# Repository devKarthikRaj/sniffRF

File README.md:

# sniffRF

## Project Snapshot
| Spec | Details |
|---|---|
| MCU | STM32L053R8 (M0+) |
| Firmware | Written in C++ via STM32CubeIDE |
| RF Detector | AD8318 Logarithmic (RF Power) Detector |
| Frequency Range | 902-928 MHz |
| Measurement Method | RF power -> Analog Voltage -> STM32 ADC |
| Power System | Li-ion battery with BQ24074 power path manager (charger included) |
| Display | OLED (SSD1306) |
| PCB | 4-layer mixed signal PCB designed in KiCad |
| Manufacturing | PCB fabrication and assembly done by JLCPCB |
| Cost | S$250 |
| Status | Hardware bring-up completed, core functionality validated (excluding OLED) |

 <br>
 <br>
 <br>
 <br>

## About
SniffRF is a simple RSSI detector aka a signal strength detector for the 902MHz to 928MHz band using an AD8318 logarithmic detector chip and built around an STM32L053R8 MCU. SniffRF displays the RSSI level on a mini OLED. SniffRF will also pulse a buzzer with varying frequency based on the RSSI level. <br>

## Sub-Systems
* RF: Input from SMA fed into AD8318 log detector. <br>
* MCU: STM32L053R8 M0+ interface circuitry, program/debug MCU via SWD.
* UI: OLED for visual feedback and buzzer for audio feedback.
* Power: 1x 18650 cell with BQ24074 power path manager, charge via USB-C, MAX1704 fuel gauge, simple buck converter for 3.3V

## Application
* SniffRF could be used to track RF transmitters using their radio signature. <br>
* SniffRF could also be used to gauge the noise floor at a particular location to select or deploy a receiver at said location. <br>   

*Note: As of now, SniffRF only tunes into the 902-928MHz band.*

## Bring-Up and Validation
* **STM32 MCU able to boot up and connect via J-Link debugger to STM32CubeIDE.** STM32 UART connection working as expected. <br>
* **AD8318 RSSI detection circuit is fully functional from about -60dBm to 0dBm. A known RF source (Sine wave transmitted at 915MHz from an Adalm Pluto SDR) was moved toward and away from the SniffRF PCB - this caused the RSSI readings to increase and decrease as expected.** <br>
* Li-Ion battery power path manager is able to charge the 18650 battery when a USB-C charge cable is plugged in. MAX1704 fuel gauge is able to read Li-Ion battery voltage + capacity and send this data over to the STM32 for display over UART. <br>
* Buzzer interfaced to STM32 is functional. <br>
* Unable to verify OLED functionality due to lack of assembled SniffRF boards, TBC... <br>

## Thoughts...
This is my first STM32 PCB! I made this PCB to learn STM32 design as well as try my hand at mixed signal PCB design. Feels good to finally strike this off my bucket list. Spent a few weekends working on this project over 3 months. More advanced RF PCBs to come!

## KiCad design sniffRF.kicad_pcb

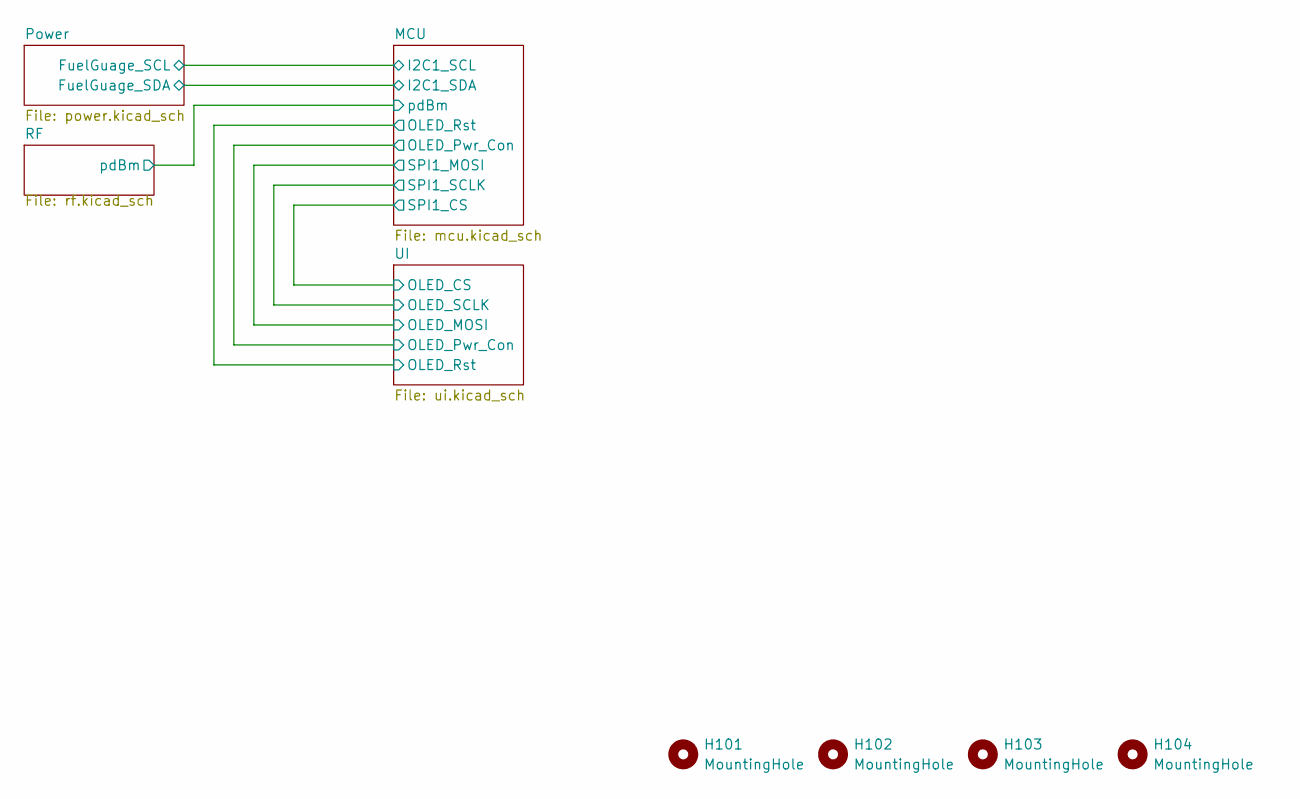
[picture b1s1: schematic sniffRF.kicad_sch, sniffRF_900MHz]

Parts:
H101, H102, H103, H104: MountingHole; MountingHole_PC104_Reinforced

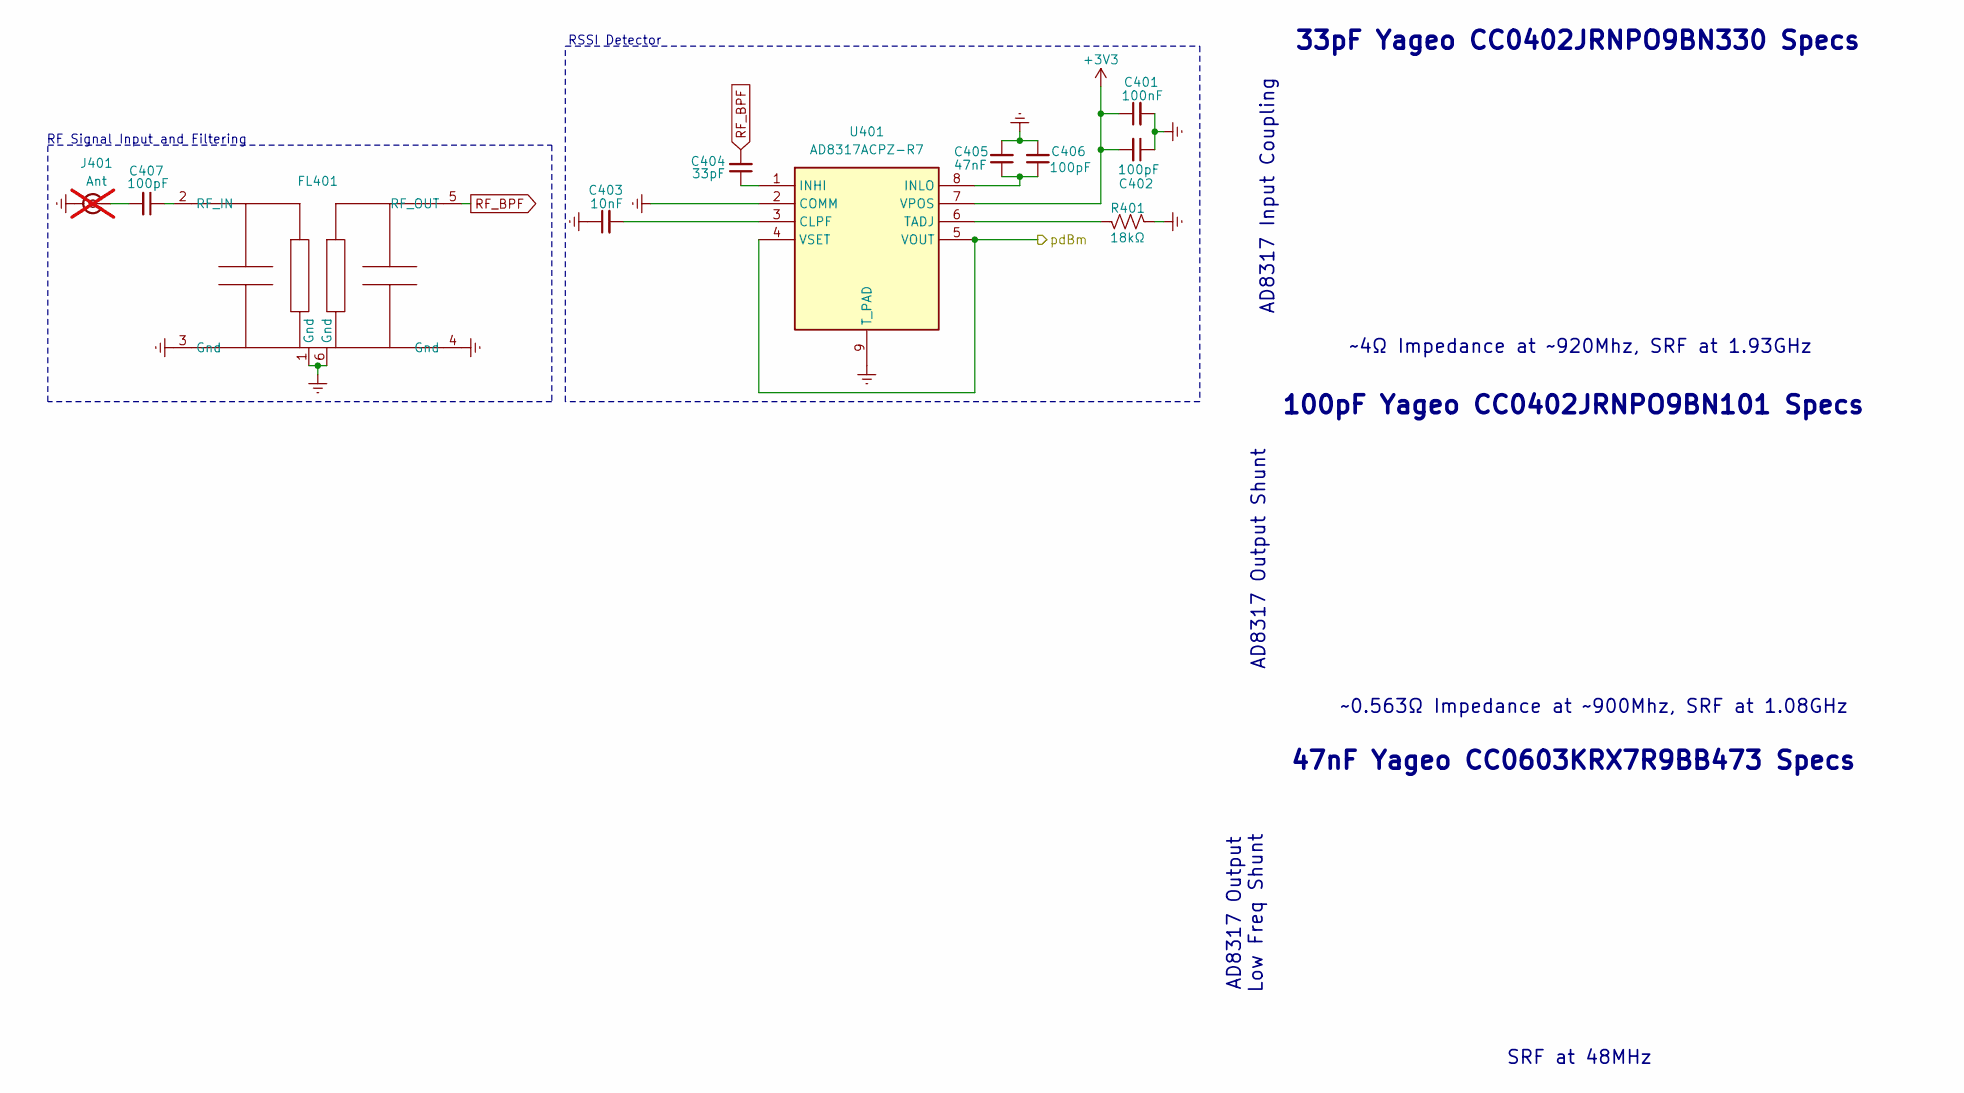
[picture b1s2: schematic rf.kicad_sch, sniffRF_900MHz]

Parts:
C401: 100nF; C_0402_1005Metric_Pad0.74x0.62mm_HandSolder; MPN CL05B104KO5NNNC; LCSC PN C1525
C402, C406, C407: 100pF; C_0402_1005Metric_Pad0.74x0.62mm_HandSolder; MPN CC0402JRNPO9BN101; LCSC PN C106200
C403: 10nF; C_0805_2012Metric_Pad1.18x1.45mm_HandSolder; MPN CC0805KRX7R9BB103; LCSC PN C83170
C404: 33pF; C_0402_1005Metric_Pad0.74x0.62mm_HandSolder; MPN CC0402JRNPO9BN330; LCSC PN C107005
C405: 47nF; C_0603_1608Metric_Pad1.08x0.95mm_HandSolder; MPN CC0603KRX7R9BB473; LCSC PN C107093
FL401: BPF_Qualcomm_B39921B3728U410; MPN B39921B3728U410; LCSC PN C2650953
J401: Ant; SMA_Cinch_142-0701-851; MPN 142-0701-801; not fitted
R401: 18kΩ; R_0603_1608Metric_Pad0.98x0.95mm_HandSolder; MPN 0603WAF1802T5E; LCSC PN C25810
U401: AD8317ACPZ-R7; RssiDet_AnalogDevices_SON50P200X300X80-9N-D; Manufacturer_Part_Number AD8317ACPZ-R7; Mouser Part Number 584-AD8317ACPZ-R7

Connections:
+3V3: C401.1, C402.2, U401.7 (VPOS); also elsewhere on the board
/MCU/pdBm: U401.4 (VSET), U401.5 (VOUT); also elsewhere on the board
GNDREF: C401.2, C402.1, C403.1, C405.2, C406.2, FL401.1 (Gnd), FL401.3 (Gnd), FL401.4 (Gnd), FL401.6 (Gnd), J401.2 (Ext), R401.2, U401.2 (COMM), U401.9 (T_PAD); also elsewhere on the board
unnamed: C407.1, FL401.2 (RF_IN)
unnamed: C407.2, J401.1 (In)
unnamed: C403.2, U401.3 (CLPF)
unnamed: C404.1, U401.1 (INHI)
unnamed: C405.1, C406.1, U401.8 (INLO)
unnamed: R401.1, U401.6 (TADJ)
RF_BPF: C404.2, FL401.5 (RF_OUT)

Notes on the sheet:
AD8317 Output Shunt
33pF Yageo CC0402JRNPO9BN330 Specs
47nF Yageo CC0603KRX7R9BB473 Specs
100pF Yageo CC0402JRNPO9BN101 Specs
~4Ω Impedance at ~920Mhz, SRF at 1.93GHz
AD8317 Output Low Freq Shunt
RF Signal Input and Filtering
~0.563Ω Impedance at ~900Mhz, SRF at 1.08GHz
SRF at 48MHz
AD8317 Input Coupling
RSSI Detector

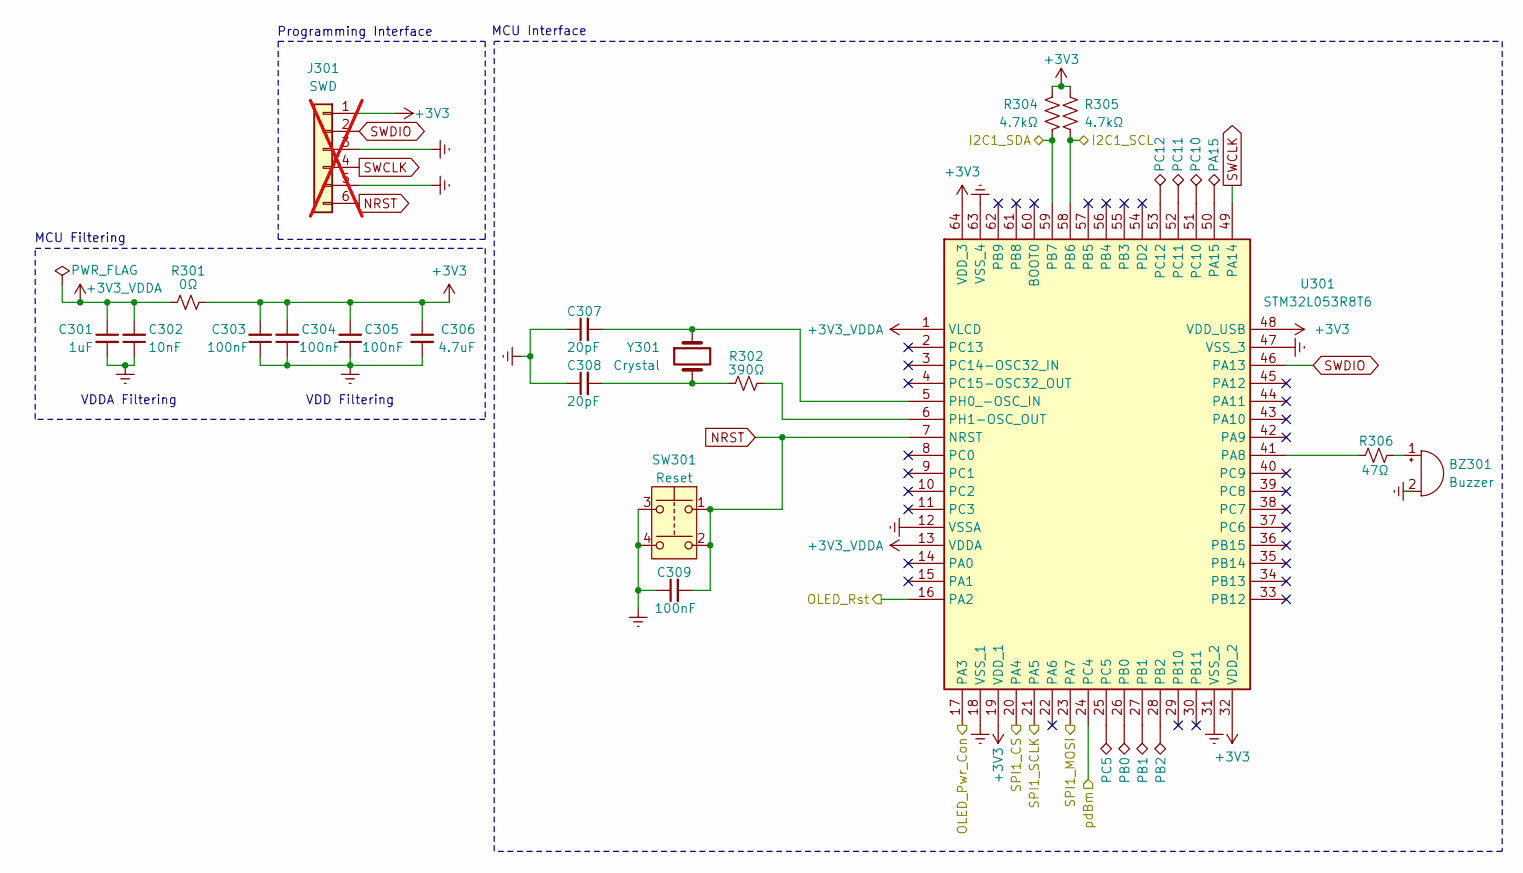
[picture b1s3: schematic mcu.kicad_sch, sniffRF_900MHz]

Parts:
BZ301: Buzzer; Buzzer_Murata_PKMCS0909E4000R1; MPN PKMCS0909E4000-R1; LCSC PN C910763
C301: 1uF; C_0603_1608Metric_Pad1.08x0.95mm_HandSolder; MPN CL10A105KB8NNNC; LCSC PN C15849
C302: 10nF; C_0402_1005Metric_Pad0.74x0.62mm_HandSolder; MPN CL05B103KB5NNNC; LCSC PN C15195
C303, C304, C305, C309: 100nF; C_0402_1005Metric_Pad0.74x0.62mm_HandSolder; MPN CL05B104KO5NNNC; LCSC PN C1525
C306: 4.7uF; C_0805_2012Metric_Pad1.18x1.45mm_HandSolder; MPN CL21A475KAQNNNE; LCSC PN C1779
C307, C308: 20pF; C_0603_1608Metric_Pad1.08x0.95mm_HandSolder; MPN CL10C200JB8NNNC; LCSC PN C1648
J301: SWD; PinHeader_1x06_P1.27mm_Vertical; not fitted
PA15: TestPoint_Alt; TestPoint_Pad_D1.0mm
PB0, PB1, PB2: TestPoint_Alt; TestPoint_Pad_D1.0mm
PC5, PC10, PC11, PC12: TestPoint_Alt; TestPoint_Pad_D1.0mm
R301: 0Ω; R_0402_1005Metric_Pad0.72x0.64mm_HandSolder; MPN 0402WGF0000TCE; LCSC PN C17168
R302: 390Ω; R_0402_1005Metric_Pad0.72x0.64mm_HandSolder; MPN RC0402FR-07390RL; LCSC PN C137997
R304, R305: 4.7kΩ; R_0603_1608Metric_Pad0.98x0.95mm_HandSolder; MPN 0603WAF4701T5E; LCSC PN C23162
R306: 47Ω; R_0603_1608Metric_Pad0.98x0.95mm_HandSolder; MPN 0603WAF470JT5E; LCSC PN C23182
SW301: Reset; Button_TE_FSM6JSMATR; MPN FSM6JSMA; LCSC PN C178262
U301: STM32L053R8T6; MCU_STM_QFP50P1200X1200X160-64N; MPN STM32L053R8T6; LCSC PN C79207
Y301: Crystal; Crystal_ECS_ECS801230QDSTR; MPN ECS-80-12-30Q-DS-TR; LCSC PN C2450805

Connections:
+3V3: C303.2, C304.2, C305.2, C306.1, J301.1, R301.2, R304.1, R305.1, U301.19 (VDD_1), U301.32 (VDD_2), U301.48 (VDD_USB), U301.64 (VDD_3); also elsewhere on the board
+3V3_VDDA: C301.1, C302.2, R301.1, U301.1 (VLCD), U301.13 (VDDA)
/MCU/I2C1_SCL: R305.2, U301.58 (PB6); also elsewhere on the board
/MCU/I2C1_SDA: R304.2, U301.59 (PB7); also elsewhere on the board
/MCU/OLED_Pwr_Con: U301.17 (PA3); also elsewhere on the board
/MCU/pdBm: U301.24 (PC4); also elsewhere on the board
/UI/CS: U301.20 (PA4); also elsewhere on the board
/UI/D0_SCLK: U301.21 (PA5); also elsewhere on the board
/UI/D1_MOSI: U301.23 (PA7); also elsewhere on the board
/UI/RES: U301.16 (PA2); also elsewhere on the board
GNDREF: BZ301.2 (-), C301.2, C302.1, C303.1, C304.1, C305.1, C306.2, C307.1, C308.1, C309.1, J301.3, J301.5, SW301.3, SW301.4, U301.12 (VSSA), U301.18 (VSS_1), U301.31 (VSS_2), U301.47 (VSS_3), U301.63 (VSS_4); also elsewhere on the board
NRST: C309.2, J301.6, SW301.1, SW301.2, U301.7 (NRST)
unnamed: BZ301.1 (+), R306.2
unnamed: C308.2, R302.1, Y301.2
unnamed: R306.1, U301.41 (PA8)
unnamed: PA15.1, U301.50 (PA15)
unnamed: PB0.1, U301.26 (PB0)
unnamed: PB1.1, U301.27 (PB1)
unnamed: PB2.1, U301.28 (PB2)
unnamed: PC5.1, U301.25 (PC5)
unnamed: PC10.1, U301.51 (PC10)
unnamed: PC11.1, U301.52 (PC11)
unnamed: PC12.1, U301.53 (PC12)
unnamed: C307.2, U301.5 (PH0_-OSC_IN), Y301.1
unnamed: R302.2, U301.6 (PH1-OSC_OUT)
SWCLK: J301.4, U301.49 (PA14)
SWDIO: J301.2, U301.46 (PA13)

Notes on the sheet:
VDD Filtering
MCU Interface
MCU Filtering
Programming Interface
VDDA Filtering

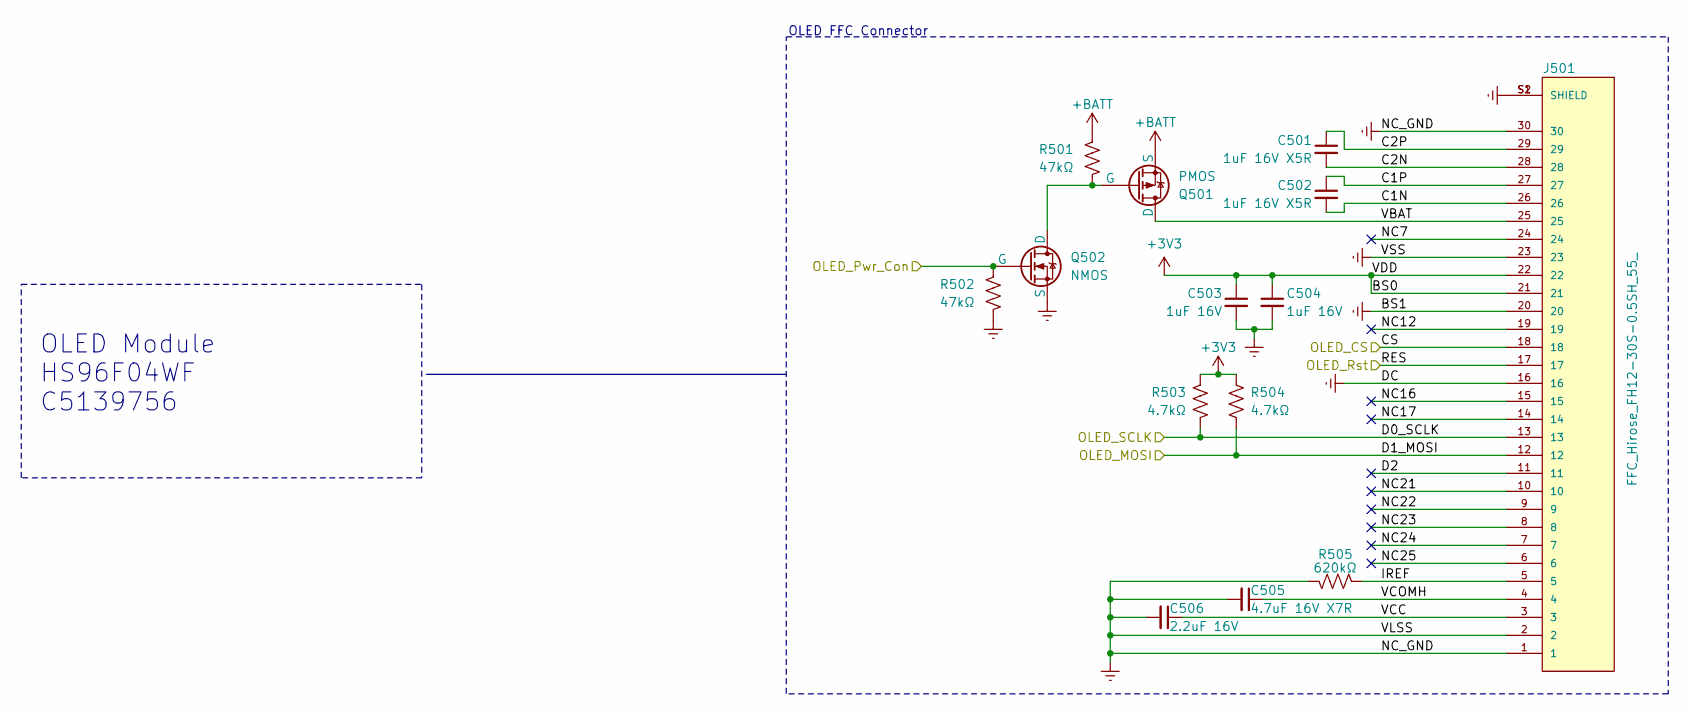
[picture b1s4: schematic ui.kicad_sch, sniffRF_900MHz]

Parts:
C501, C502: 1uF 16V X5R; C_0402_1005Metric_Pad0.74x0.62mm_HandSolder; MPN CC0402KRX5R7BB105; LCSC PN C325464
C503, C504: 1uF 16V; C_0402_1005Metric_Pad0.74x0.62mm_HandSolder; MPN CC0402KRX5R7BB105; LCSC PN C325464
C505: 4.7uF 16V X7R; C_0805_2012Metric_Pad1.18x1.45mm_HandSolder; MPN CC0805KKX7R7BB475; LCSC PN C277499
C506: 2.2uF 16V; C_0603_1608Metric_Pad1.08x0.95mm_HandSolder; MPN CL10A225KO8NNNC; LCSC PN C23630
J501: FFC_Hirose_FH12-30S-0.5SH_55_; FFC_Hirose_FH12-30S-0.5SH_55__HIROSE_FH12-30S-0.5SH_55_; MPN FH12-30S-0.5SH(55); LCSC PN C506793
Q501: PMOS; SOT-23_Handsoldering; MPN FDN338P; LCSC PN C24855
Q502: NMOS; SOT-23_Handsoldering; MPN FDN335N; LCSC PN C241804
R501, R502: 47kΩ; R_0603_1608Metric_Pad0.98x0.95mm_HandSolder; MPN 0603WAF4702T5E; LCSC PN C25819
R503, R504: 4.7kΩ; R_0805_2012Metric; MPN 0805W8F4701T5E; LCSC PN C17673
R505: 620kΩ; R_0402_1005Metric_Pad0.72x0.64mm_HandSolder; MPN RC0402FR-07620KL; LCSC PN C137952

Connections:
+3V3: C503.1, C504.1, J501.21, J501.22, R503.1, R504.1; also elsewhere on the board
+BATT: Q501.3 (S), R501.1; also elsewhere on the board
/MCU/OLED_Pwr_Con: Q502.2 (G), R502.1; also elsewhere on the board
/UI/C1N: C502.2, J501.26
/UI/C1P: C502.1, J501.27
/UI/C2N: C501.2, J501.28
/UI/C2P: C501.1, J501.29
/UI/CS: J501.18; also elsewhere on the board
/UI/D0_SCLK: J501.13, R503.2; also elsewhere on the board
/UI/D1_MOSI: J501.12, R504.2; also elsewhere on the board
/UI/D2: J501.11
/UI/IREF: J501.5, R505.1
/UI/NC7: J501.24
/UI/NC12: J501.19
/UI/NC16: J501.15
/UI/NC17: J501.14
/UI/NC21: J501.10
/UI/NC22: J501.9
/UI/NC23: J501.8
/UI/NC24: J501.7
/UI/NC25: J501.6
/UI/RES: J501.17; also elsewhere on the board
/UI/VBAT: J501.25, Q501.1 (D)
/UI/VCC: C506.1, J501.3
/UI/VCOMH: C505.1, J501.4
GNDREF: C503.2, C504.2, C505.2, C506.2, J501.1, J501.2, J501.16, J501.20, J501.23, J501.30, J501.S1 (SHIELD), J501.S2 (SHIELD), Q502.3 (S), R502.2, R505.2; also elsewhere on the board
unnamed: Q501.2 (G), Q502.1 (D), R501.2

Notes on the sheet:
OLED Module HS96F04WF C5139756
OLED FFC Connector

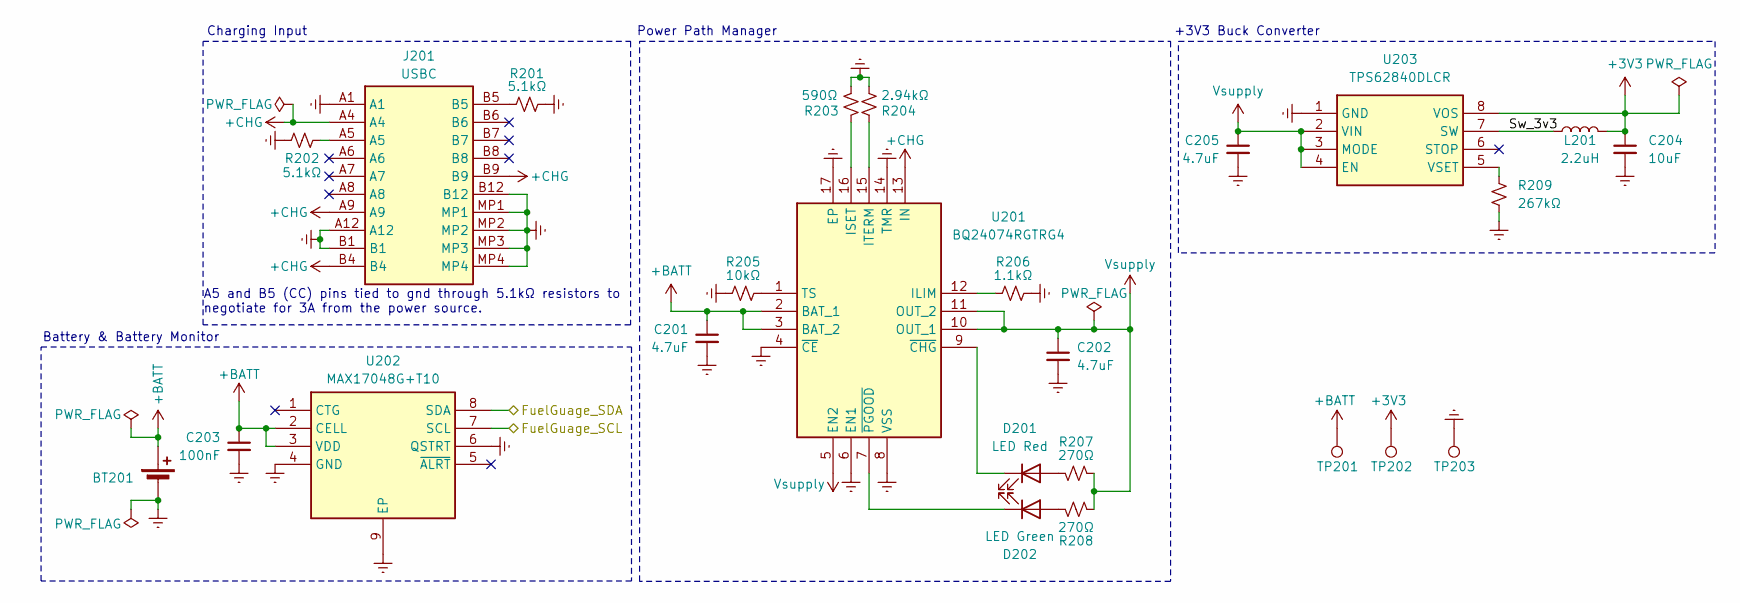
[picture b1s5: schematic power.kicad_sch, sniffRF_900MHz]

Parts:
BT201: 18650_Cell; BatteryHolder_Keystone_1043P; MPN 1043P; LCSC PN C3029535
C201, C202, C205: 4.7uF; C_0402_1005Metric_Pad0.74x0.62mm_HandSolder; MPN CL05A475MP5NRNC; LCSC PN C23733
C203: 100nF; C_0402_1005Metric_Pad0.74x0.62mm_HandSolder; MPN CL05B104KO5NNNC; LCSC PN C1525
C204: 10uF; C_0402_1005Metric_Pad0.74x0.62mm_HandSolder; MPN CL05A106MQ5NUNC; LCSC PN C15525
D201: LED Red; LED_Dialight_5973308207F; MPN 5973008207F; LCSC PN C6095189
D202: LED Green; LED_Dialight_5973308207F; MPN 5973308207F; LCSC PN C7188877
J201: USBC; Connector_GCT_USB4110GFA; MPN USB4110-GF-A; LCSC PN C5143397
L201: 2.2uH; Inductor_Murata_1286ASH1R0MP2; MPN DFE201612E-2R2M=P2; LCSC PN C337893
R201, R202: 5.1kΩ; R_0603_1608Metric_Pad0.98x0.95mm_HandSolder; MPN 0603WAF5101T5E; LCSC PN C23186
R203: 590Ω; R_0603_1608Metric_Pad0.98x0.95mm_HandSolder; MPN AC0603FR-07590RL; LCSC PN C227973
R204: 2.94kΩ; R_0402_1005Metric_Pad0.72x0.64mm_HandSolder; MPN RT0402BRD072K94L; LCSC PN C852709
R205: 10kΩ; R_0402_1005Metric_Pad0.72x0.64mm_HandSolder; MPN 0402WGJ0103TCE; LCSC PN C25531
R206: 1.1kΩ; R_0603_1608Metric_Pad0.98x0.95mm_HandSolder; MPN RT0603BRE071K1L; LCSC PN C705821
R207, R208: 270Ω; R_0805_2012Metric_Pad1.20x1.40mm_HandSolder; MPN 0805W8F2700T5E; LCSC PN C17590
R209: 267kΩ; R_1206_3216Metric_Pad1.30x1.75mm_HandSolder; MPN RT1206BRD07267KL; LCSC PN C870591
TP201, TP202, TP203: +Batt; TestPoint_Pad_D1.0mm
U201: BQ24074RGTRG4; PowerPath_TI_QFN50P300X300X100-17N-D; Manufacturer_Part_Number BQ24074RGTRG4; Mouser Part Number 595-BQ24074RGTRG4
U202: MAX17048G+T10; FuelGauge_AD_SON50P200X200X80-9N-D; MPN MAX17048G+T10; LCSC PN C2682616
U203: TPS62840DLCR; Buck_TI_SON50P150X200X100-8N-D; MPN TPS62840DLCR; LCSC PN C2071859

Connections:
+3V3: C204.1, L201.2, TP202.1, U203.8 (VOS); also elsewhere on the board
+BATT: BT201.2 (+), C201.1, C203.1, TP201.1, U201.2 (BAT_1), U201.3 (BAT_2), U202.2 (CELL), U202.3 (VDD); also elsewhere on the board
+CHG: J201.A4, J201.A9, J201.B4, J201.B9, U201.13 (IN)
/MCU/I2C1_SCL: U202.7 (SCL); also elsewhere on the board
/MCU/I2C1_SDA: U202.8 (SDA); also elsewhere on the board
/Power/Sw_3v3: L201.1, U203.7 (SW)
GNDREF: BT201.1 (-), C201.2, C202.2, C203.2, C204.2, C205.2, J201.A1, J201.A12, J201.B1, J201.B12, J201.MP1, J201.MP2, J201.MP3, J201.MP4, R201.1, R202.1, R203.1, R204.1, R205.1, R206.2, R209.2, TP203.1, U201.4 (~CE), U201.6 (EN1), U201.8 (VSS), U201.14 (TMR), U201.17 (EP), U202.4 (GND), U202.6 (QSTRT), U202.9 (EP), U203.1 (GND); also elsewhere on the board
unnamed: D201.2 (A), R207.2
unnamed: D201.1 (K), U201.9 (~CHG)
unnamed: D202.2 (A), R208.1
unnamed: D202.1 (K), U201.7 (~PGOOD)
unnamed: J201.A5, R202.2
unnamed: J201.B5, R201.2
unnamed: R206.1, U201.12 (ILIM)
unnamed: R203.2, U201.16 (ISET)
unnamed: R204.2, U201.15 (ITERM)
unnamed: R205.2, U201.1 (TS)
unnamed: R209.1, U203.5 (VSET)
Vsupply: C202.1, C205.1, R207.1, R208.2, U201.5 (EN2), U201.10 (OUT_1), U201.11 (OUT_2), U203.2 (VIN), U203.3 (MODE), U203.4 (EN)

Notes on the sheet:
A5 and B5 (CC) pins tied to gnd through 5.1kΩ resistors to negotiate for 3A from the power source.
Charging Input
Battery & Battery Monitor
+3V3 Buck Converter
Power Path Manager

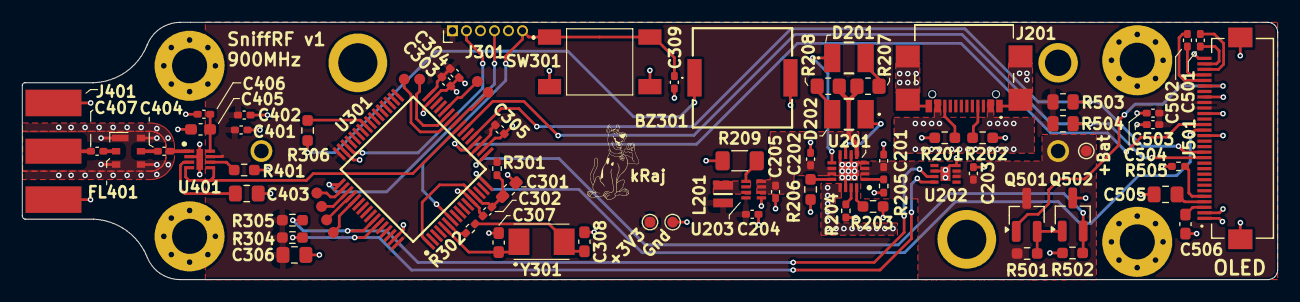
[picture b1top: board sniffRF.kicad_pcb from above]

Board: 4 copper layers, 113.8 x 23.3 mm, 81 parts (1 on the bottom side), 58 nets.

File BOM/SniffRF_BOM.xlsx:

Reference | Qty | Value | Manufacturer | MPN | Supplier | SPN | Alt Supplier | Alt SPN | LCSC PN | DNP
BT201 | 1 | 18650_Cell | Keystone | 1043P |  |  |  |  | C3029535
BZ301 | 1 | Buzzer | Murata | PKMCS0909E4000-R1 |  |  |  |  | C910763
C201,C202,C205 | 3 | 4.7uF | Samsung | CL05A475MP5NRNC |  |  |  |  | C23733
C203,C303,C304,C305,C309,C401 | 6 | 100nF | Samsung | CL05B104KO5NNNC |  |  |  |  | C1525
C204 | 1 | 10uF | Samsung | CL05A106MQ5NUNC |  |  |  |  | C15525
C301 | 1 | 1uF | Samsung | CL10A105KB8NNNC |  |  |  |  | C15849
C302 | 1 | 10nF | Samsung | CL05B103KB5NNNC |  |  |  |  | C15195
C306 | 1 | 4.7uF | Samsung | CL21A475KAQNNNE |  |  |  |  | C1779
C307,C308 | 2 | 20pF | Samsung | CL10C200JB8NNNC |  |  |  |  | C1648
C402,C406,C407 | 3 | 100pF | Yageo | CC0402JRNPO9BN101 |  |  |  |  | C106200
C403 | 1 | 10nF | Yageo | CC0805KRX7R9BB103 |  |  |  |  | C83170
C404 | 1 | 33pF | Yageo | CC0402JRNPO9BN330 |  |  |  |  | C107005
C405 | 1 | 47nF | Yageo | CC0603KRX7R9BB473 |  |  |  |  | C107093
C501,C502 | 2 | 1uF 16V X5R | Yageo | CC0402KRX5R7BB105 |  |  |  |  | C325464
C503,C504 | 2 | 1uF 16V | Yageo | CC0402KRX5R7BB105 |  |  |  |  | C325464
C505 | 1 | 4.7uF 16V X7R | Yageo | CC0805KKX7R7BB475 |  |  |  |  | C277499
C506 | 1 | 2.2uF 16V | Samsung | CL10A225KO8NNNC |  |  |  |  | C23630
D201 | 1 | LED Red | Dialight | 5973008207F |  |  |  |  | C6095189
D202 | 1 | LED Green | Dialight | 5973308207F |  |  |  |  | C7188877
FL401 | 1 | ~ | Qualcomm | B39921B3728U410 |  |  |  |  | C2650953
H101,H102,H103,H104 | 4 | MountingHole
J201 | 1 | USBC | Global Connector Technology | USB4110-GF-A |  |  |  |  | C5143397
J301 | 1 | SWD |  |  |  |  |  |  |  | DNP
J401 | 1 | Ant | Cinch Connectivity Solutions Johnson | 142-0701-801 | DigiKey | J502-ND |  |  |  | DNP
J501 | 1 | FFC_Hirose_FH12-30S-0.5SH_55_ | Hirose | FH12-30S-0.5SH(55) |  |  |  |  | C506793
L201 | 1 | 2.2uH | Murata | DFE201612E-2R2M=P2 |  |  |  |  | C337893
PA15,PB0,PB1,PB2,PC5,PC10,PC11,PC12 | 8 | TestPoint_Alt
Q501 | 1 | PMOS | OnSemi | FDN338P |  |  |  |  | C24855
Q502 | 1 | NMOS | OnSemi | FDN335N |  |  |  |  | C241804
R201,R202 | 2 | 5.1kΩ | UNI-ROYAL | 0603WAF5101T5E |  |  |  |  | C23186
R203 | 1 | 590Ω | Yageo | AC0603FR-07590RL |  |  |  |  | C227973
R204 | 1 | 2.94kΩ | Yageo | RT0402BRD072K94L |  |  |  |  | C852709
R205 | 1 | 10kΩ | UNI-ROYAL | 0402WGJ0103TCE |  |  |  |  | C25531
R206 | 1 | 1.1kΩ | Yageo | RT0603BRE071K1L |  |  |  |  | C705821
R207,R208 | 2 | 270Ω | UNI-ROYAL | 0805W8F2700T5E |  |  |  |  | C17590
R209 | 1 | 267kΩ | Yageo | RT1206BRD07267KL |  |  |  |  | C870591
R301 | 1 | 0Ω | UNI-ROYAL | 0402WGF0000TCE |  |  |  |  | C17168
R302 | 1 | 390Ω | Yageo | RC0402FR-07390RL |  |  |  |  | C137997
R304,R305 | 2 | 4.7kΩ | UNI-ROYAL | 0603WAF4701T5E |  |  |  |  | C23162
R306 | 1 | 47Ω | UNI-ROYAL | 0603WAF470JT5E |  |  |  |  | C23182
R401 | 1 | 18kΩ | UNI-ROYAL | 0603WAF1802T5E |  |  |  |  | C25810
R501,R502 | 2 | 47kΩ | UNI-ROYAL | 0603WAF4702T5E |  |  |  |  | C25819
R503,R504 | 2 | 4.7kΩ | UNI-ROYAL | 0805W8F4701T5E |  |  |  |  | C17673
R505 | 1 | 620kΩ | Yageo | RC0402FR-07620KL |  |  |  |  | C137952
SW301 | 1 | Reset | TE Connectivity | FSM6JSMA |  |  |  |  | C178262
TP201,TP202,TP203 | 3 | +Batt
U201 | 1 | BQ24074RGTRG4 | Texas Instruments | BQ24074RGTR |  |  |  |  | C54313
U202 | 1 | MAX17048G+T10 | Analog Devices | MAX17048G+T10 |  |  |  |  | C2682616
U203 | 1 | TPS62840DLCR | Texas Instruments | TPS62840DLCR |  |  |  |  | C2071859
U301 | 1 | STM32L053R8T6 | ST Microelectronics | STM32L053R8T6 |  |  |  |  | C79207
U401 | 1 | AD8317ACPZ-R7 | Analog Devices | AD8317ACPZ-R7 |  |  |  |  | C578693
Y301 | 1 | Crystal | ECS | ECS-80-12-30Q-DS-TR |  |  |  |  | C2450805

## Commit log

2025-12-24 Updated readme and file structure, bug fixes and prep for manuf
2025-12-27 Added pdf sch and layout, updated file struc
2026-03-04 Updated readme and media
2026-03-04 Added media and updated readme
